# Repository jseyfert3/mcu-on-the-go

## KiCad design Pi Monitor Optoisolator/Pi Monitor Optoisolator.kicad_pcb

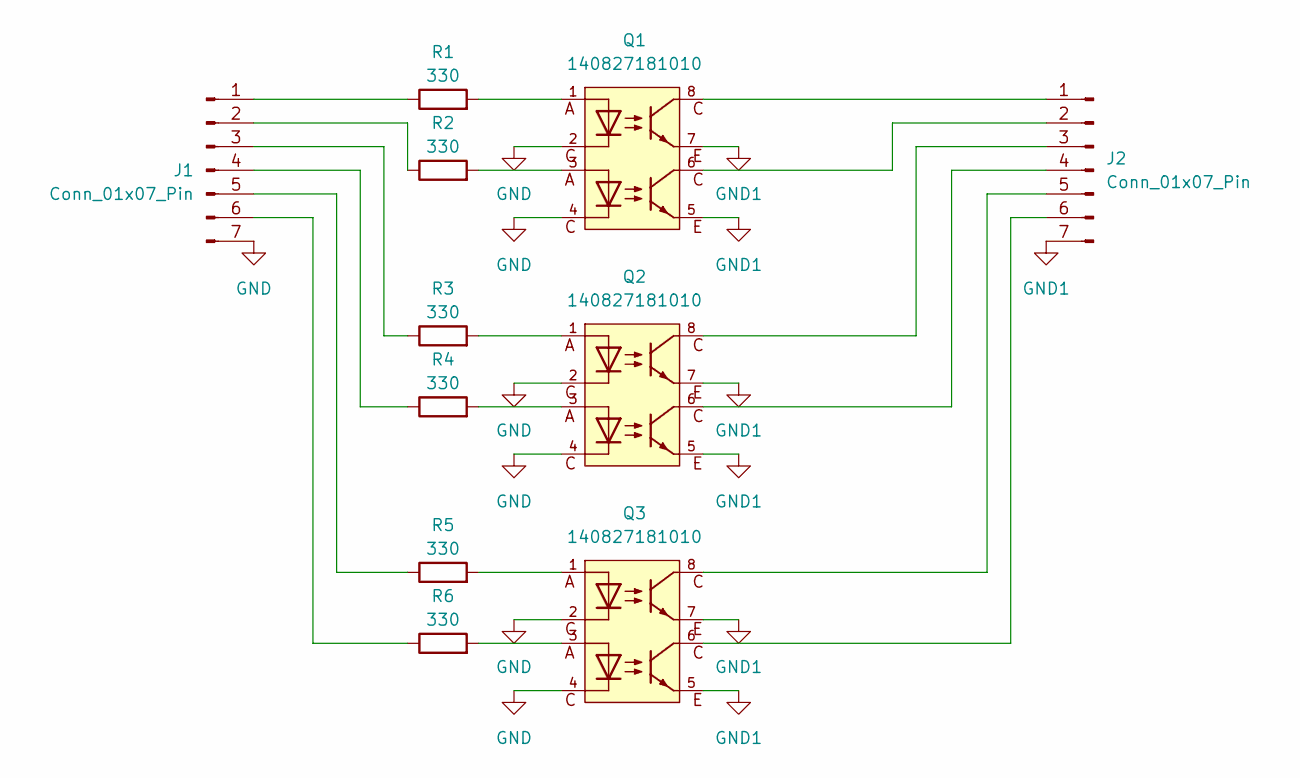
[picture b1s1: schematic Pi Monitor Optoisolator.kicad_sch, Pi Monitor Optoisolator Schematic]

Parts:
J1, J2: Conn_01x07_Pin; PinHeader_1x07_P2.54mm_Vertical
Q1, Q2, Q3: 140827181010; WL-OCPT_DIP8_M-TYPE
R1, R2, R3, R4, R5, R6: 330; R_Axial_DIN0207_L6.3mm_D2.5mm_P7.62mm_Horizontal

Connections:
GND: J1.7, Q1.2, Q1.4, Q2.2, Q2.4, Q3.2, Q3.4
GND1: J2.7, Q1.5, Q1.7, Q2.5, Q2.7, Q3.5, Q3.7
unnamed: J1.1, R1.1
unnamed: J1.2, R2.1
unnamed: J1.3, R3.1
unnamed: J1.4, R4.1
unnamed: J1.5, R5.1
unnamed: J1.6, R6.1
unnamed: J2.1, Q1.8
unnamed: J2.2, Q1.6
unnamed: J2.3, Q2.8
unnamed: J2.4, Q2.6
unnamed: J2.5, Q3.8
unnamed: J2.6, Q3.6
unnamed: Q1.1, R1.2
unnamed: Q1.3, R2.2
unnamed: Q2.1, R3.2
unnamed: Q2.3, R4.2
unnamed: Q3.1, R5.2
unnamed: Q3.3, R6.2

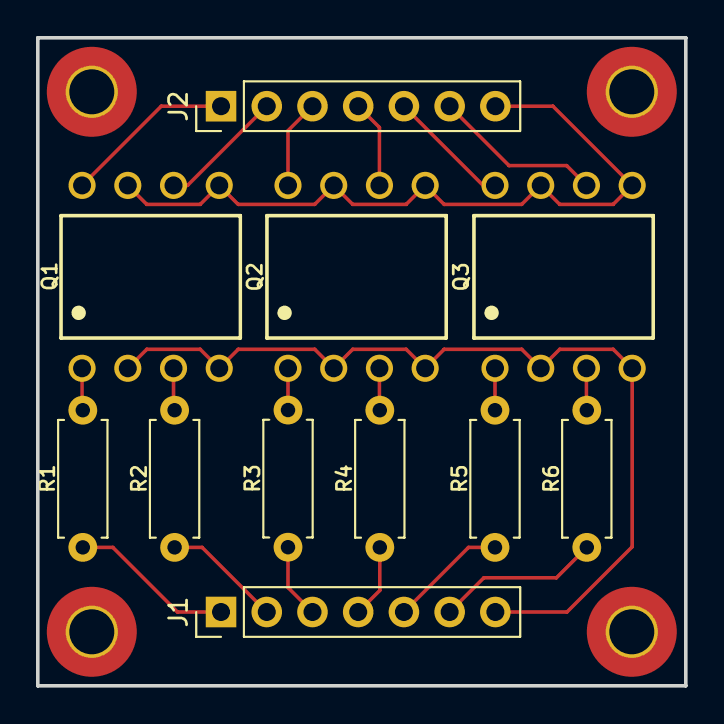
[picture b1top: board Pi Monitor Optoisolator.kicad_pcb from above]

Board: 2 copper layers, 36.0 x 36.0 mm, 11 parts (0 on the bottom side), 20 nets.

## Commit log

2025-07-19 New: Pi Monitor Optoisolator
    Added the simple PCB circuit design for an optoisolator to allow MCU or Pi control of the Pi Monitor.
2025-07-19 Minor adjustments
    * Renamed LICENSE to COPYING (I wish GitHub would ask you what you wanted to name the license file)
    * Added a COPYRIGHT NOTICE for the Pi Monitor Optoisolator. I did this as a seperate file, because unlike actual code files, there's not a ton of room for lots of text in a schematic or PCB drawing f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
    * Update .gitignore file
2025-07-19 fix: Updated PN of optoisolator
2025-07-19 feat: Shrunk edge cuts to save ~$1 at OSHPark

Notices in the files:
Pi Monitor Optoisolator/Pi Monitor Optoisolator.kicad_pcb:
Released under GPL-3.0-or-later license
Copyright 2025 Jonathan Seyfert
